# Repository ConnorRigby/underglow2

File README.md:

# Underglow 2

Automotive PMU designed for controlling external lighting.

## Specs

|high side output|low side output|12v digital input|BLE|Radio|
|-|-|-|-|-|
|2|6|4|1|1|

## Repository Structure

|folder|description|
|-|-|
|[docs](docs/README.md)|Documentation for hardware as well as 3d models and interactive bill of materials|
|[hardware](hardware/README.md)|Source material for the hardware PCB design|

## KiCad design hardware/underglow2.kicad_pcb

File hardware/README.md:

# coneRGB Underglow Controller Hardware Design

Source material for the PCB design. Designed using KiCAD intended to
be produced at PCBWay using parts from LCSC.

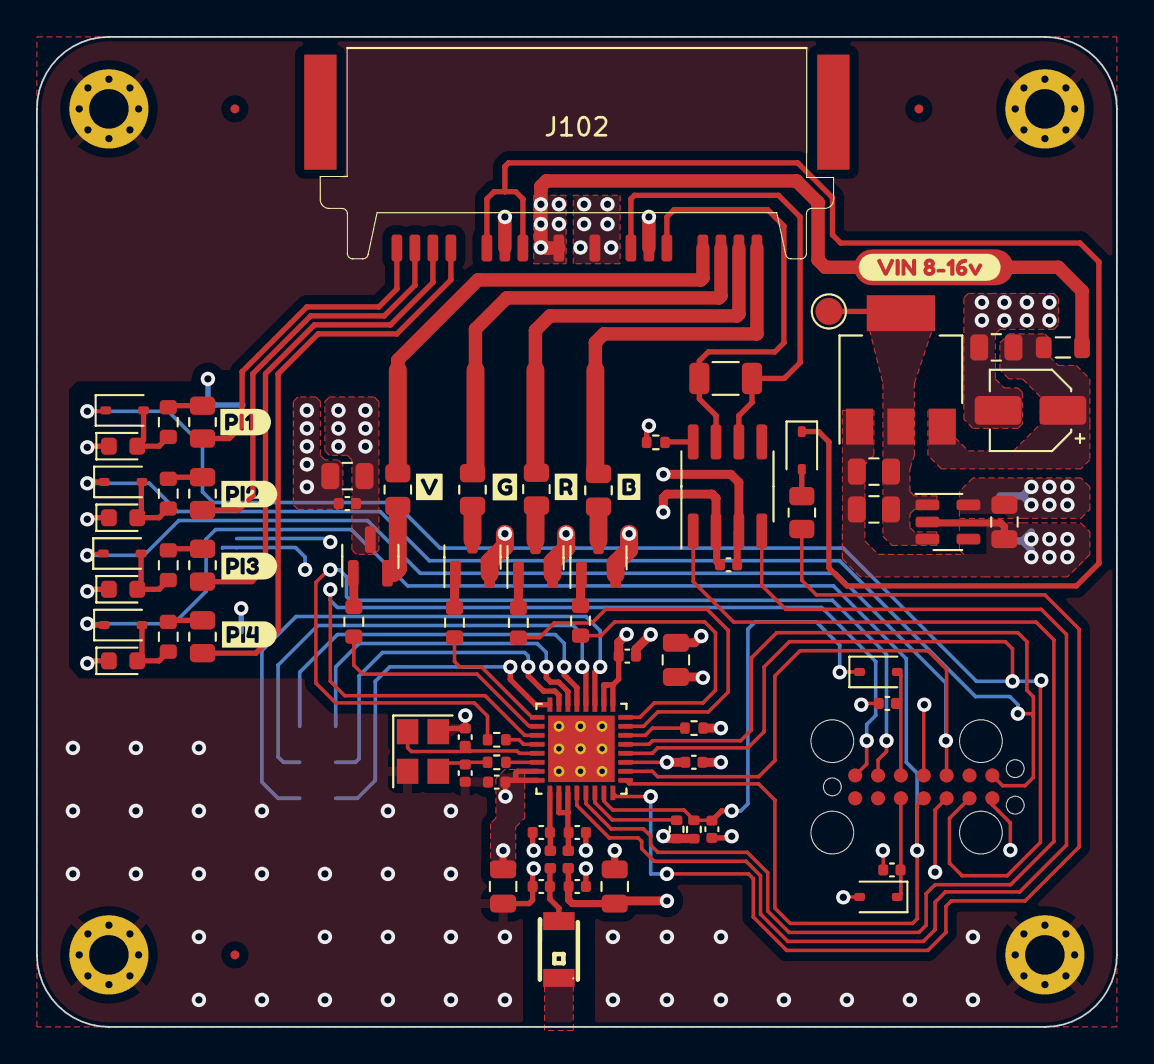
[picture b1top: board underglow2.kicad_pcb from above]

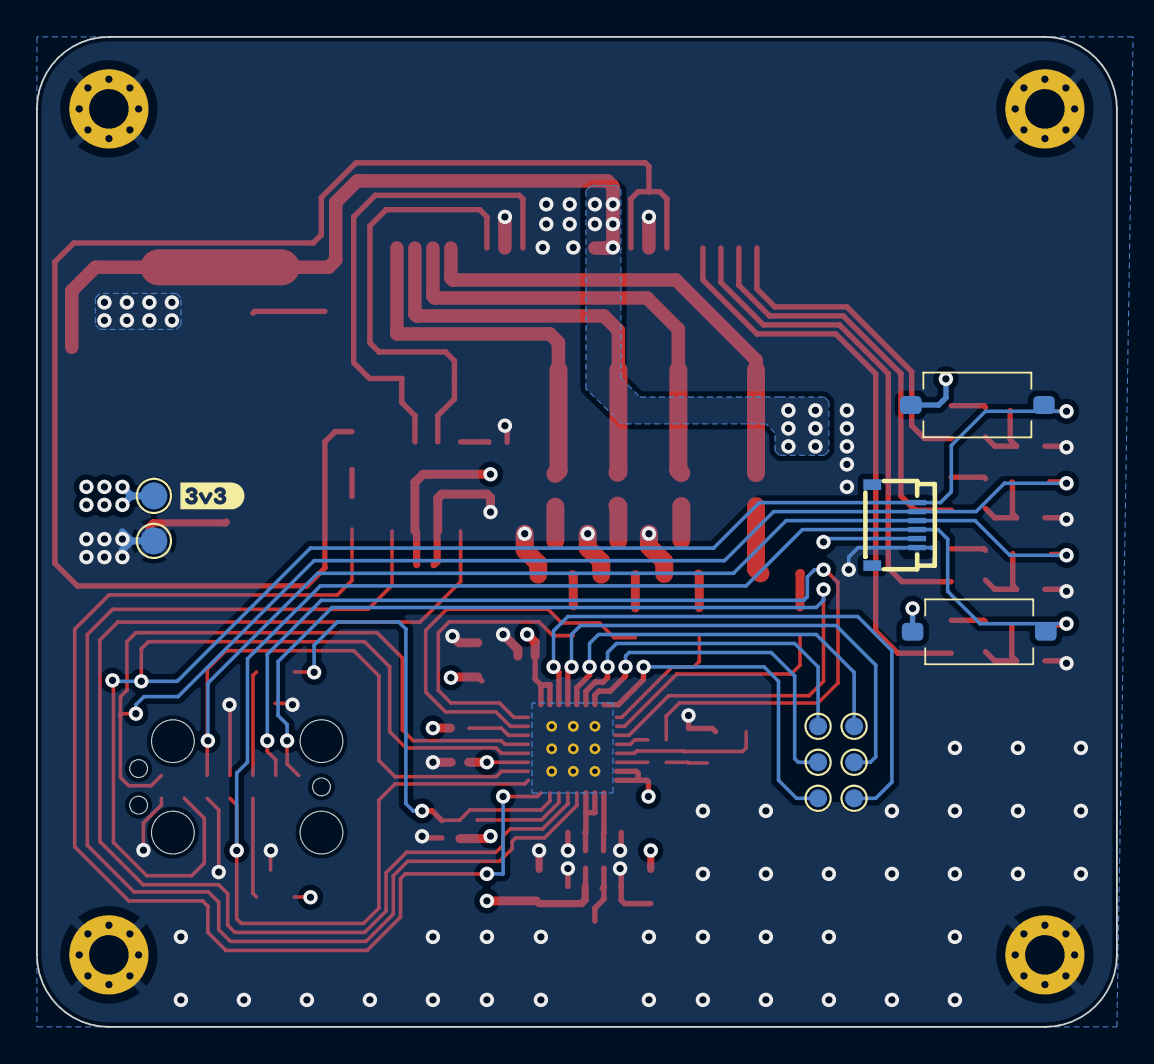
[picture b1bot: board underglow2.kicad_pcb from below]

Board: 4 copper layers, 60.0 x 55.0 mm, 99 parts (12 on the bottom side), 65 nets.

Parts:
AE101: Antenna_Chip; ANT-SMD_L3.2-W1.6
C1: 22uF; CP_Elec_4x5.4
C2, C108, C117: C_0805_10u_X5R; C_0805_2012Metric
C3, C116: 4.7uF; C_0805_2012Metric
C101, C106, C113: C_0805_1u_X7R; C_0805_2012Metric
C102, C103, C109, C110, C114, C115, C118, C119, C120: C_0402_100nf_X7R; C_0402_1005Metric
C104, C105: C_0402_18p_NP0; C_0402_1005Metric
C107: C_0402_10n_C0G; C_0402_1005Metric
C111, C112: C_0402_3p3_C0G; C_0402_1005Metric
D101, D104, D105, D106: LED_0603_RED; LED_0603_1608Metric
D102, D107, D108, D109, D110, D111, D112: 1N5819WS; D_SOD-323
FB101: 300mΩ ±25% 600Ω@100MHz; L_0805_2012Metric
H101, H102, H103, H104: MountingHole; MountingHole_2.2mm_M2_Pad_Via
J101: Conn_ST_STDC14; TC2070-IDC-FP
J102: ZE05H-16DP-2H
J104: FH34SRJ-6S-0.5SH(50); FFC-SMD_6P-P0.50_FH34SRJ-6S-0.5SH
L101: 2nH; L_0402_1005Metric
L102: 2.2nH; L_0402_1005Metric
Q101: AO3401A; SOT-23
Q102, Q103, Q104: AO3400A; SOT-23
R101, R108, R109, R110: R_0805_100; R_0805_2012Metric
R102, R113, R115, R116: R_0805_10k; R_0805_2012Metric
R103, R114, R117, R118: R_0603_1k; R_0603_1608Metric
R104, R105, R106, R107: R_0603_100; R_0603_1608Metric
R111: R_0603_220; R_0805_2012Metric
R119, R123, R124, R125: R_0402_1k; R_0402_1005Metric
R120: R_1206_DNP; R_1206_3216Metric
R121: R_0402_0; R_0402_1005Metric
R122: R_0402_499; R_0402_1005Metric
SW101, SW104: TS-1101-C-W; TS1101CW
TP1, TP2, TP3: TestPoint; TestPoint_Pad_D1.5mm
TP4, TP5, TP6, TP7, TP8, TP9: TestPoint; TestPoint_Pad_D1.0mm
U1: SPX3819M5-L-3-3/TR; SOT-23-5
U101: ESP32-C3FH4; QFN50P500X500X90-33N
U102: SN65HVD230; SOIC-8_3.9x4.9mm_P1.27mm
U103: SPX1117M3-L-5-0/TR; SOT-223-3_TabPin2
Y101: 40_Mhz; Crystal_SMD_3225-4Pin_3.2x2.5mm
kibuzzard-648F92C0: G***; kibuzzard-648F92C0
kibuzzard-648F92CD: G***; kibuzzard-648F92CD
kibuzzard-648F92E2: G***; kibuzzard-648F92E2
kibuzzard-648F92EC: G***; kibuzzard-648F92EC
kibuzzard-648F93A2: G***; kibuzzard-648F93A2
kibuzzard-648F93D4: G***; kibuzzard-648F93D4
kibuzzard-648F933E: G***; kibuzzard-648F933E
kibuzzard-648F9315: G***; kibuzzard-648F9315
kibuzzard-648F9323: G***; kibuzzard-648F9323
kibuzzard-648F9331: G***; kibuzzard-648F9331

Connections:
+5V: C2.1, C116.1, TP1.1, U1.1 (IN), U1.3 (EN), U103.2 (VO)
/B_GATE: R107.1, U101.16 (GPIO10)
/B_OUT: J102.6, R110.2
/CAN_H: J102.14, R120.1, U102.7 (CANH)
/CAN_L: J102.13, R120.2, U102.6 (CANL)
/CAN_RXD: U101.4 (XTAL_32K_P), U102.4 (R)
/CAN_TXD: U101.5 (XTAL_32K_N), U102.1 (D)
/EN: C120.1, D107.1 (K), R123.2, U101.7 (CHIP_EN)
/G_GATE: R106.1, U101.25 (GPIO18)
/G_OUT: J102.5, R109.2
/JTRST: C119.1, D107.2 (A), J101.12 (~RST)
/LNA_IN: C111.1, L102.1, U101.1 (LNA_IN)
/MTCK: D111.1 (K), J101.6 (JCLK/SWCLK), J104.6, SW104.1, U101.12 (MTCK)
/MTDI: D110.1 (K), J101.10 (JTDI/NC), J104.4, U101.10 (MTDI)
/MTDO: D112.1 (K), J101.8 (JTDO/SWO), J104.5, U101.13 (MTDO)
/MTMS: D108.1 (K), J101.4 (JTMS/SWDIO), J104.3, SW101.1, U101.9 (MTMS)
/NRZ1: R111.1, U101.8 (GPIO3)
/NZR1_OUT: D102.1 (K), J102.9, J102.10
/PI1: J102.8, R102.1
/PI1_DIV: D101.2 (A), D108.2 (A), R103.2
/PI2: J102.2, R113.1
/PI2_DIV: D104.2 (A), D110.2 (A), R114.2
/PI3: J102.7, R115.1
/PI3_DIV: D105.2 (A), D112.2 (A), R117.2
/PI4: J102.1, R116.1
/PI4_DIV: D106.2 (A), D111.2 (A), R118.2
/RF_ANT: AE101.2 (PCB_Trace), C112.1, L102.2
/R_GATE: R105.1, U101.15 (GPIO9)
/R_OUT: J102.16, R108.2
/SPICLK: TP7.1, U101.22 (SPICLK)
/SPICS0: TP6.1, U101.21 (SPICS0)
/SPID: TP8.1, U101.23 (SPID)
/SPIHD: TP4.1, U101.19 (SPIHD)
/SPIQ: TP9.1, U101.24 (SPIQ)
/SPIWP: TP5.1, U101.20 (SPIWP)
/VCP_RX: J101.14 (VCP_TX), U101.27 (U0RXD)
/VCP_TX: J101.13 (VCP_RX), R122.2
/V_GATE: R104.1, U101.26 (GPIO19)
/V_OUT: J102.15, R101.2
/XTAL_N: C105.1, U101.29 (XTAL_N), Y101.1
/XTAL_P: R121.2, U101.30 (XTAL_P)
/_VCP_TX: R122.1, U101.28 (U0TXD)
/_XTAL_P: C104.1, R121.1, Y101.3
GND: C1.2, C2.2, C3.2, C101.2, C102.2, C103.2, C104.2, C105.2, C106.2, C107.2, C108.2, C109.2, C110.2, C111.2, C112.2, C113.2, C114.2, C115.2, C116.2, C117.2, C118.2, C119.2, C120.2, D101.1 (K), D104.1 (K), D105.1 (K), D106.1 (K), H101.1, H102.1, H103.1, H104.1, J101.5 (GND), J101.7 (GND), J101.11 (GNDDetect), J102.3, J102.4, J102.12, J104.1, Q102.2 (S), Q103.2 (S), Q104.2 (S), R119.2, TP3.1, U1.2 (GND), U101.33 (GND), U102.2 (GND), U103.1 (GND), Y101.2, Y101.4
unnamed: C110.1, L101.1, U101.2 (VDD3P3), U101.3 (VDD3P3)
unnamed: D102.2 (A), R111.2
unnamed: C118.1, D109.1 (K), J101.3 (VCC)
unnamed: Q101.1 (G), R104.2
unnamed: Q101.2 (S), R101.1
unnamed: Q102.3 (D), R108.1
unnamed: Q102.1 (G), R105.2
unnamed: Q103.3 (D), R109.1
unnamed: Q103.1 (G), R106.2
unnamed: Q104.3 (D), R110.1
unnamed: Q104.1 (G), R107.2
unnamed: R102.2, R103.1
unnamed: R113.2, R114.1
unnamed: R115.2, R117.1
unnamed: R116.2, R118.1
unnamed: R124.2, U101.6 (GPIO2)
unnamed: R125.2, U101.14 (GPIO8)
unnamed: R119.1, U102.8 (Rs)
unnamed: C1.1, C3.1, FB101.2, U103.3 (VI)
VDD: C103.1, C106.1, C107.1, C108.1, C109.1, C113.1, C114.1, C115.1, C117.1, D109.2 (A), J104.2, L101.2, R123.1, R124.1, R125.1, SW101.2, SW104.2, TP2.1, U1.5 (OUT), U101.11 (VDD3P3_RTC), U101.17 (VDD3P3_CPU), U101.18 (VDD_SPI), U101.31 (VDDA), U101.32 (VDDA), U102.3 (VCC)
VS: C101.1, C102.1, FB101.1, J102.11, Q101.3 (D)

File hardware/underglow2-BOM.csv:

Item,Qty,Reference(s),Value,LibPart,Footprint,Datasheet,DNP,Capacitance,Color,Frequency,LCSC,MOSFET_TYPE,MPN,Resistance,Temperature,Tolerance,Voltage
1,1,AE101,Antenna_Chip,Device:Antenna_Chip,LCSC_Antenna:ANT-SMD_L3.2-W1.6,https://datasheet.lcsc.com/lcsc/1810241140_YAGEO-ANT3216LL00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,,,,,C293767,,C293767,,,,
2,1,C1,22uF,Device:C_Polarized_Small,Capacitor_SMD:CP_Elec_4x5.4,https://datasheet.lcsc.com/lcsc/2304140030_ROQANG-RVT1C220M0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,,,,,C72502,,RVT1C220M0405,,,,
3,3,"C2, C108, C117",C_0805_10u_X5R,LCSC_Capacitor:C_0805_10u_X5R,Capacitor_SMD:C_0805_2012Metric,https://datasheet.lcsc.com/lcsc/2304140030_Samsung-Electro-M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,,10uF,,,C15850,,CL21A106KAYNNNE,,X5R,10%,35V
4,2,"C3, C116",4.7uF,Device:C_Small,Capacitor_SMD:C_0805_2012Metric,https://datasheet.lcsc.com/lcsc/2304140030_Samsung-Electro-M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,,,,,C1779,,CL21A475KAQNNNE,,,,
5,8,"C103, C109, C110, C114, C115, C118, C119, C120",C_0402_100nf_X7R,LCSC_Capacitor:C_0402_100nf_X7R,Capacitor_SMD:C_0402_1005Metric,https://datasheet.lcsc.com/lcsc/2304140030_Samsung-Electro-M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,,100nf,,,C1525,,CL05B104KO5NNNC,,X7R,,50V
6,2,"C104, C105",C_0402_18p_NP0,LCSC_Capacitor:C_0402_DNP,Capacitor_SMD:C_0402_1005Metric,https://datasheet.lcsc.com/lcsc/2304140030_FH--Guangdong-Fen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,,18pF,,,C1549,,0402CG180J500NT,,,,
7,2,"C106, C113",C_0805_1u_X7R,LCSC_Capacitor:C_0805_1u_X7R,Capacitor_SMD:C_0805_2012Metric,https://datasheet.lcsc.com/lcsc/2304140030_Samsung-Electro-M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,,1uF,,,C28323,,CL21B105KBFNNNE,,X7R,10%,16V
8,1,C107,C_0402_10n_C0G,LCSC_Capacitor:C_0402_10n_C0G,Capacitor_SMD:C_0402_1005Metric,https://datasheet.lcsc.com/lcsc/2304140030_Samsung-Electro-M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,,10nf,,,C15195,,CL05B103KB5NNNC,,C0G,±5%,35V
9,2,"C111, C112",C_0402_3p3_C0G,LCSC_Capacitor:C_0402_DNP,Capacitor_SMD:C_0402_1005Metric,https://datasheet.lcsc.com/lcsc/2304140030_FH--Guangdong-Fen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,,3.3pF,,,C1565,,0402CG3R3C500NT,,,,
10,4,"D101, D104, D105, D106",LED_0603_RED,LCSC_LED:LED_0603_RED,LED_SMD:LED_0603_1608Metric,https://datasheet.lcsc.com/lcsc/1912111437_MEIHUA-MHT192CRCT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,,,Red,,C389517,,MHT192CRCT,,,,
11,7,"D102, D107, D108, D109, D110, D111, D112",1N5819WS,Diode:1N5819WS,Diode_SMD:D_SOD-323,https://datasheet.lcsc.com/lcsc/2204281430_Guangdong-Hottech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,,,,,C191023,,1N5819WS,,,,
12,1,FB101,300mΩ ±25% 600Ω@100MHz,Device:FerriteBead_Small,Inductor_SMD:L_0805_2012Metric,https://datasheet.lcsc.com/lcsc/2109181830_Sunlord-GZ2012D60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,,,,,C1017,,GZ2012D601TF,,,,
13,1,J102,ZE05H-16DP-2H,Connector_Generic_MountingPin:Conn_01x16_MountingPin,Harness:ZE05-16DS-HU,https://datasheet.lcsc.com/lcsc/2211031030_HRS-Hirose-ZE05H-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,,,,,C5242960,,ZE05H-16DP-2H,,,,
14,1,J103,ZE05-16DS-HU/R,Connector_Generic_MountingPin:Conn_01x16_MountingPin,Harness:ZE05-16DS-HU,~,,,,,C3267442,,ZE05-16DS-HU/R,,,,
15,1,L101,2nH,Device:L_Small,Inductor_SMD:L_0402_1005Metric,https://datasheet.lcsc.com/lcsc/2304140030_Chilisin-Elec-CLH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,,,,,C142239,,CLH1005T-2N0S-S-NP,,,,
16,1,L102,2.2nH,Device:L_Small,Inductor_SMD:L_0402_1005Metric,https://datasheet.lcsc.com/lcsc/2304140030_Chilisin-Elec-CLH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,,,,,C142238,,CLH1005T-2N2S-S-NP,,,,
17,1,Q101,AO3401A,Transistor_FET:AO3401A,Package_TO_SOT_SMD:SOT-23,http://www.aosmd.com/pdfs/datasheet/AO3401A.pdf,,,,,C15127,P-Channel,AO3401A,,,,
18,3,"Q102, Q103, Q104",AO3400A,Transistor_FET:AO3400A,Package_TO_SOT_SMD:SOT-23,http://www.aosmd.com/pdfs/datasheet/AO3400A.pdf,,,,,C20917,N-Channel,AO3400A,,,,
19,4,"R101, R108, R109, R110",R_0805_100,LCSC_Resistor:R_0805_DNP,Resistor_SMD:R_0805_2012Metric,https://datasheet.lcsc.com/lcsc/2206010216_UNI-ROYAL-Uniroya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,,,,,C17408,,0805W8F1000T5E,100Ω,,,
20,4,"R102, R113, R115, R116",R_0805_10k,LCSC_Resistor:R_0805_10k,Resistor_SMD:R_0805_2012Metric,https://datasheet.lcsc.com/lcsc/2206010216_UNI-ROYAL-Uniroya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,,,,,C17414,,0805W8F1002T5E,10kΩ,,,
21,4,"R103, R114, R117, R118",R_0603_1k,LCSC_Resistor:R_0603_DNP,Resistor_SMD:R_0603_1608Metric,https://datasheet.lcsc.com/lcsc/2206010130_UNI-ROYAL-Uniroya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,,,,,C21190,,0603WAF1001T5E,1kΩ,,,
22,4,"R104, R105, R106, R107",R_0603_100,LCSC_Resistor:R_0603_DNP,Resistor_SMD:R_0603_1608Metric,https://datasheet.lcsc.com/lcsc/2206010130_UNI-ROYAL-Uniroya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,,,,,C22775,,0603WAF1000T5E,100Ω,,,
23,1,R111,R_0603_220,LCSC_Resistor:R_0805_DNP,Resistor_SMD:R_0805_2012Metric,https://datasheet.lcsc.com/lcsc/2304140030_YAGEO-RC0603FR-07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,,,,,C17557,,0805W8F2200T5E,220Ω,,,
24,4,"R119, R123, R124, R125",R_0402_1k,LCSC_Resistor:R_0402_1k,Resistor_SMD:R_0402_1005Metric,https://datasheet.lcsc.com/lcsc/2206010216_UNI-ROYAL-Uniroya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,,,,,C11702,,0402WGF1001TCE,1kΩ,,,
25,1,R121,R_0402_0,LCSC_Resistor:R_0402_DNP,Resistor_SMD:R_0402_1005Metric,https://datasheet.lcsc.com/lcsc/2206010216_UNI-ROYAL-Uniroya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,,,,,C17168,,0402WGF0000TCE,0Ω,,,
26,1,R122,R_0402_499,LCSC_Resistor:R_0402_499,Resistor_SMD:R_0402_1005Metric,https://datasheet.lcsc.com/lcsc/2202281730_YAGEO-RT0402BRD07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,,,,,C852807,,RT0402BRD07499RL,499Ω,,,
27,16,"T101, T102, T103, T104, T105, T106, T107, T108, T109, T110, T111, T112, T113, T114, T115, T116",ZE05-2022SCF,Connector:Conn_01x01_Pin,Harness:ZE05-2022SCF,~,,,,,C570453,,ZE05-2022SCF,,,,
28,1,U1,SPX3819M5-L-3-3/TR,Regulator_Linear:SPX3819M5-L-3-3,Package_TO_SOT_SMD:SOT-23-5,https://datasheet.lcsc.com/lcsc/2304140030_MaxLinear-SPX3819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,,,,,C9055,,SPX3819M5-L-3-3/TR,,,,
29,1,U101,ESP32-C3FH4,LCSC_Microcontroller:ESP32-C3FH4,LCSC_Microcontroller:QFN50P500X500X90-33N,https://www.mouser.com/datasheet/2/891/esp32_c3_datasheet_en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,,,,,C2858491,,ESP32-C3FH4,,,,
30,1,U102,SN65HVD230,Interface_CAN_LIN:SN65HVD230,Package_SO:SOIC-8_3.9x4.9mm_P1.27mm,http://www.ti.com/lit/ds/symlink/sn65hvd230.pdf,,,,,C12084,,SN65HVD230DR,,,,
31,1,U103,SPX1117M3-L-5-0/TR ,Regulator_Linear:AP1117-50,Package_TO_SOT_SMD:SOT-223-3_TabPin2,https://datasheet.lcsc.com/lcsc/2304140030_MaxLinear-SPX1117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,,,,,C6187,,SPX1117M3-L-5-0/TR,,,,
32,1,Y101,40_Mhz,LCSC_Crystal:40_Mhz,Crystal:Crystal_SMD_3225-4Pin_3.2x2.5mm,https://datasheet.lcsc.com/lcsc/2110101030_Shenzhen-SCTF-Ele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,,,,40Mhz,C2901712,,SX3B40.000F1210F30,,,,

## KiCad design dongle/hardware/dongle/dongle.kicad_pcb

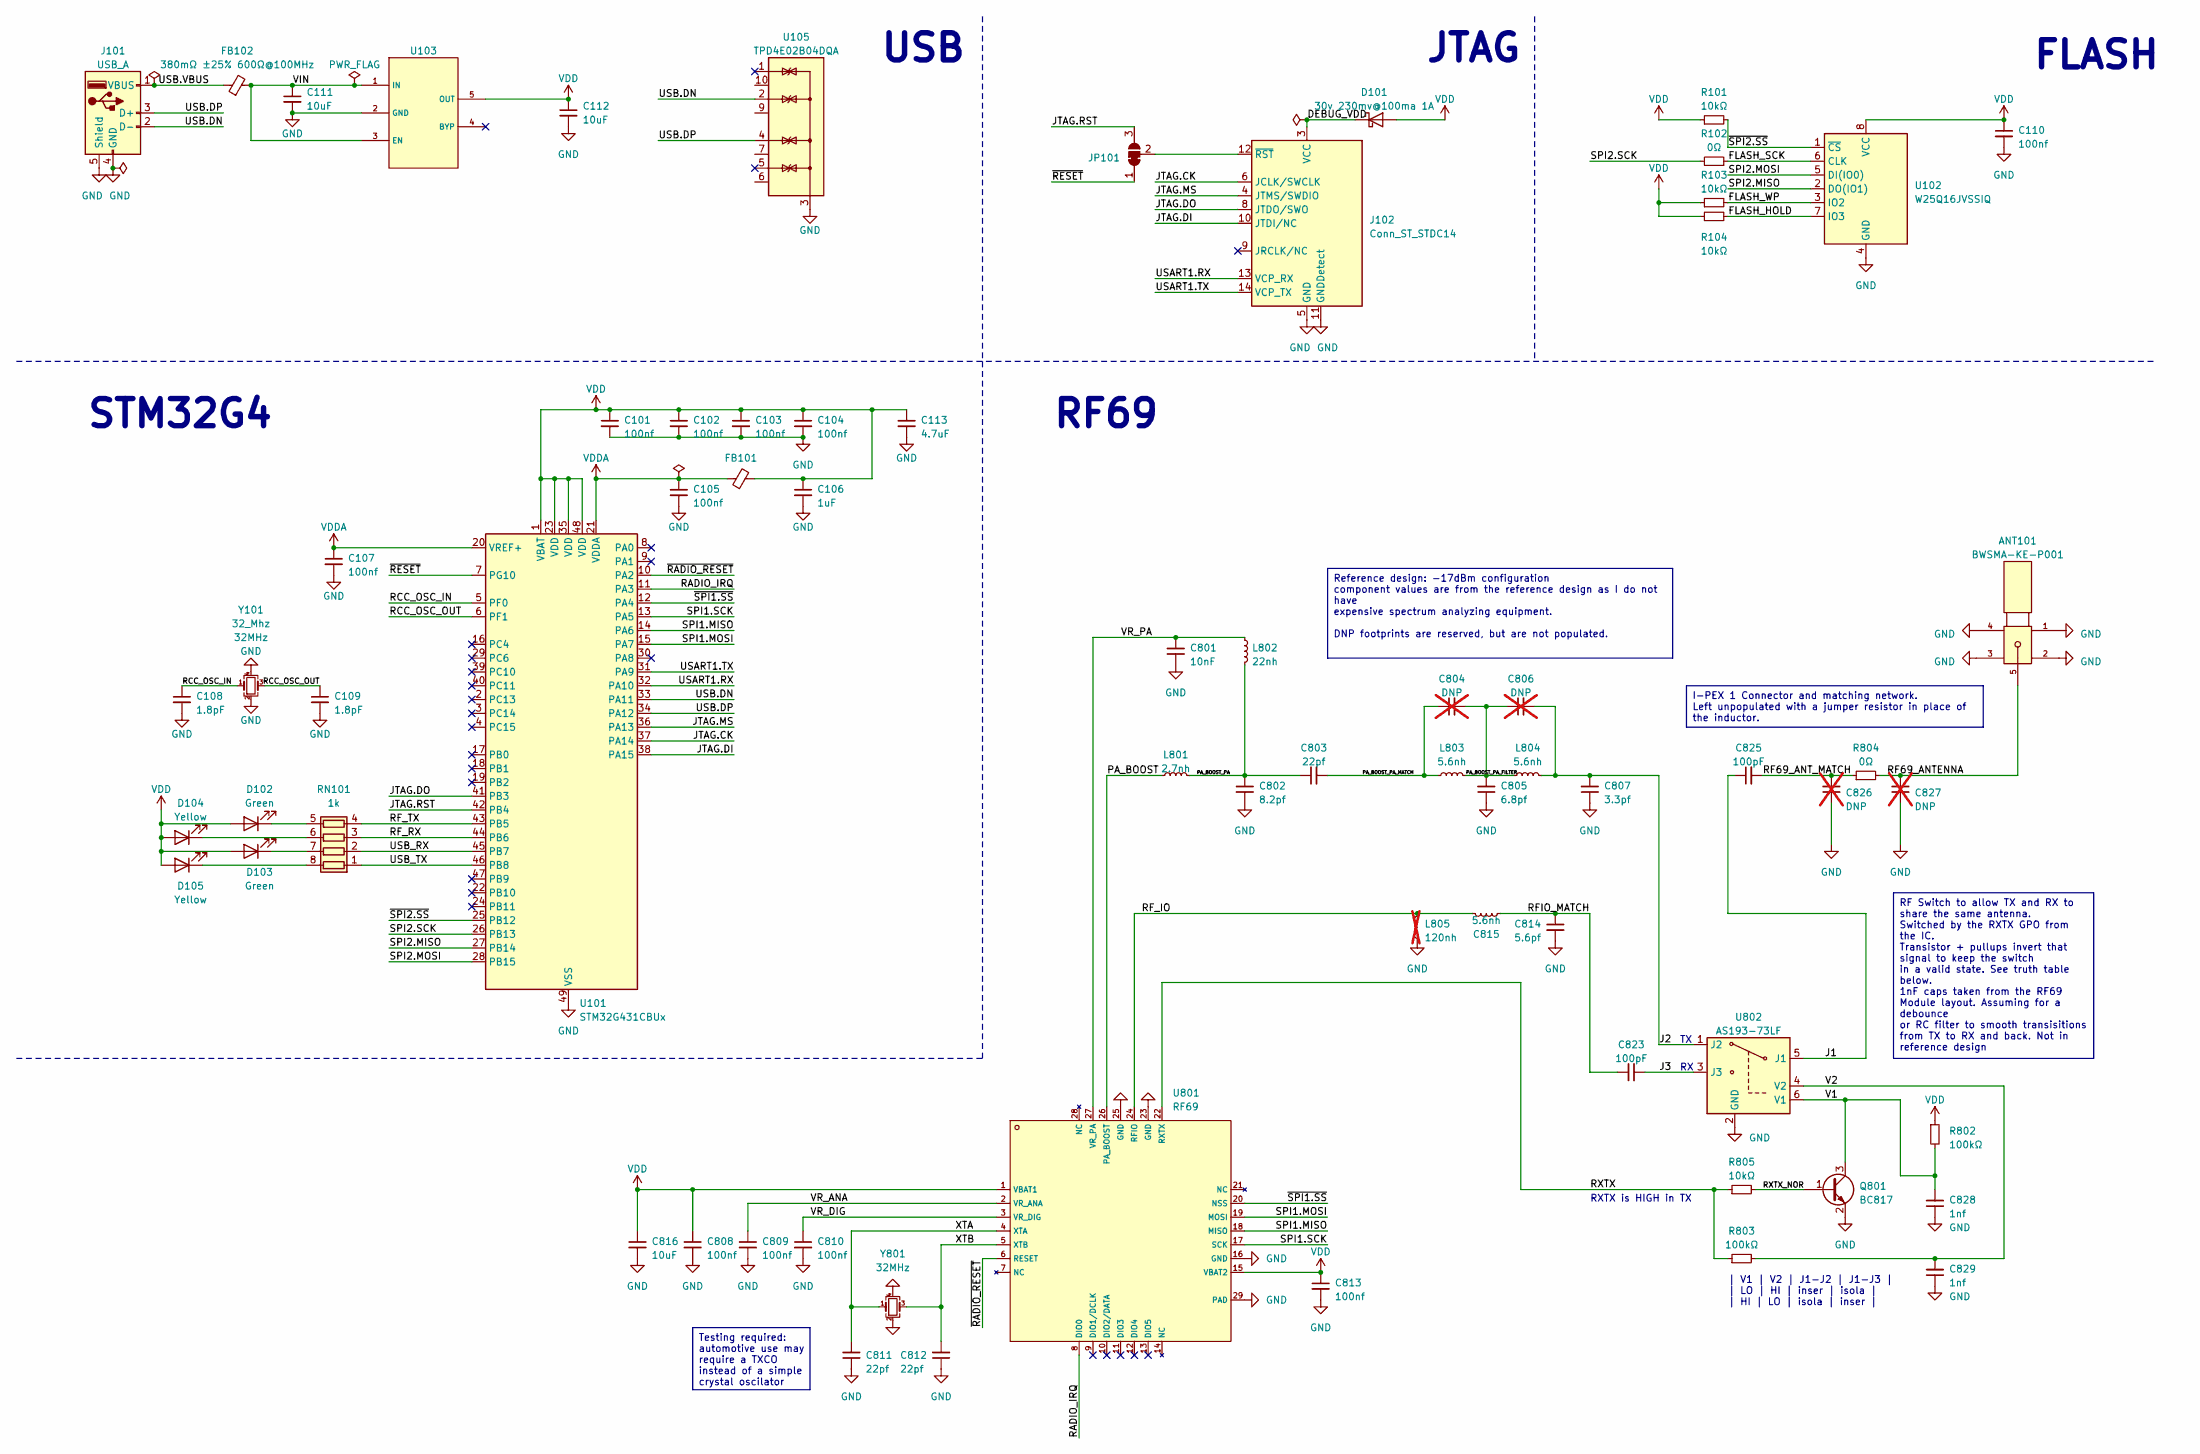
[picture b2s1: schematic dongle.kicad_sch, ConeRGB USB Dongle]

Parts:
ANT101: BWSMA-KE-P001; SMA-SMD_BWSMA-KE-P001; LCSC C496550
C101, C102, C103, C104, C105, C107, C110, C808, C809, C810, C813: C_0402_100nf_X7R; C_0402_1005Metric; Voltage 50V; MPN 0402B104K500NT; LCSC C110251
C106: C_0402_1u_X5R; C_0402_1005Metric; Voltage 35V; MPN CL05A105KL5NRNC; LCSC C307413
C108, C109: C_0402_1p8_C0G; C_0402_1005Metric; Voltage 50V; Tolerance 1%; MPN GJM1555C1H1R8WB01D; LCSC C76903
C111, C112, C816: C_0805_10u_X5R; C_0805_2012Metric; Voltage 35V; Tolerance 10%; MPN GRM21BR6YA106KE43L; LCSC C162422
C113: C_0805_4u7_X5R; C_0805_2012Metric; Voltage 6.3; Tolerance 20%; MPN CC0805MKX5R5BB475; LCSC C577033
C801: C_0402_10n_C0G; C_0402_1005Metric; Voltage 50V; Tolerance ±10%; MPN CC0402KRX7R9BB103; LCSC C60133
C802: C_0402_8p2_C0G; C_0402_1005Metric; Voltage 50V; Tolerance 2%; MPN GJM1555C1H8R2CB01D; LCSC C88898
C803, C811, C812: C_0402_22p_C0G; C_0402_1005Metric; Voltage 50V; Tolerance 2%; MPN GJM1555C1H220GB01D; LCSC C161315
C804, C806, C826, C827: C_0402_DNP; C_0402_1005Metric; not fitted
C805: C_0402_6p8_C0G; C_0402_1005Metric; Voltage 50V; Tolerance 2%; MPN GCM1555C1H6R8BA16D; LCSC C354360
C807: C_0402_3p3_C0G; C_0402_1005Metric; Voltage 50V; Tolerance 2%; MPN GRM1555C1H3R3CA01D; LCSC C76968
C814: C_0402_5p6_C0G; C_0402_1005Metric; Voltage 50V; Tolerance 2%; MPN GJM1555C1H5R6CB01D; LCSC C88895
C815: L_0402_5n6; L_0402_1005Metric; MPN LQW15AN5N6C10D; LCSC C91626
C823, C825: C_0402_100p_C0G; C_0402_1005Metric; Voltage 50V; Tolerance 5%; MPN GRT1555C1H101JA02D; LCSC C711072
C828, C829: C_0402_1nf_X7R; C_0402_1005Metric; Voltage 100V; MPN GCM155R72A102KA37D; LCSC C126538
D101: 30v 230mv@100ma 1A; D_SOD-323F; MPN CUS10S30,H3F; LCSC C146335
D102, D103: LED_0603_GREEN; LED_0603_1608Metric; MPN MHT192UGCT; LCSC C389519
D104, D105: LED_0603_YELLOW; LED_0603_1608Metric; MPN 19-213/Y2C-CQ2R2L/3T(CY); LCSC C72038
FB101: L_0402_1005Metric; LCSC C102745
FB102: 380mΩ ±25% 600Ω@100MHz; L_0603_1608Metric; LCSC C19330
J101: USB_A; USB-A-TH_48037-0001; LCSC C136455
J102: Conn_ST_STDC14; TC2070-IDC-FP
JP101: SolderJumper_3_Bridged12; SolderJumper-3_P1.3mm_Bridged12_RoundedPad1.0x1.5mm_NumberL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
L801: L_0402_2n7; L_0402_1005Metric; MPN LQW15AN2N7C00D; LCSC C98058
L802: L_0402_22n; L_0402_1005Metric; MPN LQW15AN22NG00D; LCSC C86129
L803, L804: L_0402_5n6; L_0402_1005Metric; MPN LQW15AN5N6C10D; LCSC C91626
L805: L_0402_120n; L_0402_1005Metric; MPN LQW15ANR12J00D; LCSC C113123; not fitted
Q801: BC817; SOT-23; LCSC C39828
R101, R103, R104, R805: R_0402_10k; R_0402_1005Metric; MPN ARG02BTC1002; LCSC C2902636
R102, R804: R_0402_0; R_0402_1005Metric; MPN RTT020000FTH; LCSC C102745
R802, R803: R_0402_100k; R_0402_1005Metric; MPN ARG02BTC1003; LCSC C2984406
RN101: 1k; R_Array_Concave_4x0603; LCSC C20197
U101: STM32G431CBUx; QFN-48-1EP_7x7mm_P0.5mm_EP5.6x5.6mm; LCSC C529356
U102: W25Q16JVSSIQ; SOIC-8_5.23x5.23mm_P1.27mm; MPN W25Q16JVSSIQ; LCSC C82317
U103: SPX3819M5-L-3-3_TR; SOT-23-5; LCSC C9055
U105: TPD4E02B04DQA; USON-10_2.5x1.0mm_P0.5mm; MPN TPD4E02B04DQA; LCSC C106794
U801: RF69; QFN-28-1EP_5x5mm_P0.5mm_EP3.75x3.75mm_ThermalVias; MPN RF69; LCSC C77220
U802: AS193-73LF; SOT-23-6; MPN AS193-73LF; LCSC C6199
Y101: 32_Mhz; Crystal_SMD_3225-4Pin_3.2x2.5mm; MPN TAXM32M4RLBCDT2T; LCSC C5143379
Y801: 32_Mhz; Crystal_SMD_3225-4Pin_3.2x2.5mm; MPN X322532MOB4SI; LCSC C9009

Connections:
/DEBUG_VDD: D101.1 (K), J102.3 (VCC)
/FLASH_HOLD: R104.2, U102.7 (IO3)
/FLASH_SCK: R102.1, U102.6 (CLK)
/FLASH_WP: R103.2, U102.3 (IO2)
/J1: C825.1, U802.5 (J1)
/J2: C806.2, C807.2, L804.2, U802.1 (J2)
/J3: C823.2, U802.3 (J3)
/JTAG.CK: J102.6 (JCLK/SWCLK), U101.37 (PA14)
/JTAG.DI: J102.10 (JTDI/NC), U101.38 (PA15)
/JTAG.DO: J102.8 (JTDO/SWO), U101.41 (PB3)
/JTAG.MS: J102.4 (JTMS/SWDIO), U101.36 (PA13)
/JTAG.RST: JP101.3 (B), U101.42 (PB4)
/PA_BOOST: L801.1, U801.26 (PA_BOOST)
/PA_BOOST_PA: C802.1, C803.1, L801.2, L802.2
/PA_BOOST_PA_FILTER: C804.2, C805.2, C806.1, L803.2, L804.1
/PA_BOOST_PA_MATCH: C803.2, C804.1, L803.1
/RADIO_IRQ: U101.11 (PA3), U801.8 (DIO0)
/RCC_OSC_IN: C108.1, U101.5 (PF0), Y101.1
/RCC_OSC_OUT: C109.1, U101.6 (PF1), Y101.3
/RF69_ANTENNA: ANT101.5, C827.2, R804.2
/RF69_ANT_MATCH: C825.2, C826.2, R804.1
/RFIO_MATCH: C814.1, C815.1, C823.1
/RF_IO: C815.2, L805.2, U801.24 (RFIO)
/RF_RX: RN101.3 (R3.1), U101.44 (PB6)
/RF_TX: RN101.4 (R4.1), U101.43 (PB5)
/RXTX: R803.1, R805.1, U801.22 (RXTX)
/RXTX_NOR: Q801.1 (B), R805.2
/SPI1.MISO: U101.14 (PA6), U801.18 (MISO)
/SPI1.MOSI: U101.15 (PA7), U801.19 (MOSI)
/SPI1.SCK: U101.13 (PA5), U801.17 (SCK)
/SPI2.MISO: U101.27 (PB14), U102.2 (DO(IO1))
/SPI2.MOSI: U101.28 (PB15), U102.5 (DI(IO0))
/SPI2.SCK: R102.2, U101.26 (PB13)
/USART1.RX: J102.13 (VCP_RX), U101.32 (PA10)
/USART1.TX: J102.14 (VCP_TX), U101.31 (PA9)
/USB.DN: J101.2 (D-), U101.33 (PA11); also elsewhere on the board
/USB.DP: J101.3 (D+), U101.34 (PA12); also elsewhere on the board
/USB.VBUS: FB102.1, J101.1 (VBUS)
/USB_RX: RN101.2 (R2.1), U101.45 (PB7)
/USB_TX: RN101.1 (R1.1), U101.46 (PB8)
/V1: C828.2, Q801.3 (C), R802.2, U802.6 (V1)
/V2: C829.2, R803.2, U802.4 (V2)
/VIN: C111.1, FB102.2, U103.1 (IN), U103.3 (EN)
/VR_ANA: C809.1, U801.2 (VR_ANA)
/VR_DIG: C810.1, U801.3 (VR_DIG)
/VR_PA: C801.1, L802.1, U801.27 (VR_PA)
/XTA: C811.2, U801.4 (XTA), Y801.1
/XTB: C812.2, U801.5 (XTB), Y801.3
/~RADIO_RESET: U101.10 (PA2), U801.6 (RESET)
/~RESET: JP101.1 (A), U101.7 (PG10)
/~SPI1.SS: U101.12 (PA4), U801.20 (NSS)
/~SPI2.SS: R101.2, U101.25 (PB12), U102.1 (~CS)
GND: ANT101.1, ANT101.2, ANT101.3, ANT101.4, C101.2, C102.2, C103.2, C104.2, C105.2, C106.2, C107.2, C108.2, C109.2, C110.2, C111.2, C112.2, C113.2, C801.2, C802.2, C805.1, C807.1, C808.2, C809.2, C810.2, C811.1, C812.1, C813.2, C814.2, C816.2, C826.1, C827.1, C828.1, C829.1, J101.4 (GND), J101.5 (Shield), J102.5 (GND), J102.7 (GND), J102.11 (GNDDetect), L805.1, Q801.2 (E), U101.49 (VSS), U102.4 (GND), U103.2 (GND), U801.16 (GND), U801.23 (GND), U801.25 (GND), U801.29 (PAD), U802.2 (GND), Y101.2, Y101.4, Y801.2, Y801.4; also elsewhere on the board
unnamed: D102.1 (K), RN101.5 (R4.2)
unnamed: D103.1 (K), RN101.7 (R2.2)
unnamed: D104.1 (K), RN101.6 (R3.2)
unnamed: D105.1 (K), RN101.8 (R1.2)
unnamed: J102.12 (~RST), JP101.2 (C)
VDD: C101.1, C102.1, C103.1, C104.1, C106.1, C110.1, C112.1, C113.1, C808.1, C813.1, C816.1, D101.2 (A), D102.2 (A), D103.2 (A), D104.2 (A), D105.2 (A), FB101.2, R101.1, R103.1, R104.1, R802.1, U101.1 (VBAT), U101.23 (VDD), U101.35 (VDD), U101.48 (VDD), U102.8 (VCC), U103.5 (OUT), U801.1 (VBAT1), U801.15 (VBAT2)
VDDA: C105.1, C107.1, FB101.1, U101.20 (VREF+), U101.21 (VDDA)

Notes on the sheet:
I-PEX 1 Connector and matching network. Left unpopulated with a jumper resistor in place of the inductor.
Testing required: automotive use may require a TXCO instead of a simple crystal oscilator
RF Switch to allow TX and RX to share the same antenna. Switched by the RXTX GPO from the IC. Transistor + pullups invert that signal to keep the switch in a valid state. See truth table below. 1nF caps taken from the RF69 Module layout. Assuming for a debounce or RC filter to smooth transisitions 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
Reference design: -17dBm configuration component values are from the reference design as I do not have expensive spectrum analyzing equipment. DNP footprints are reserved, but are not populated.
RF69
FLASH
STM32G4
JTAG
USB
RXTX is HIGH in TX
| V1 | V2 | J1-J2 | J1-J3 | | LO | HI | inser | isola | | HI | LO | isola | inser |

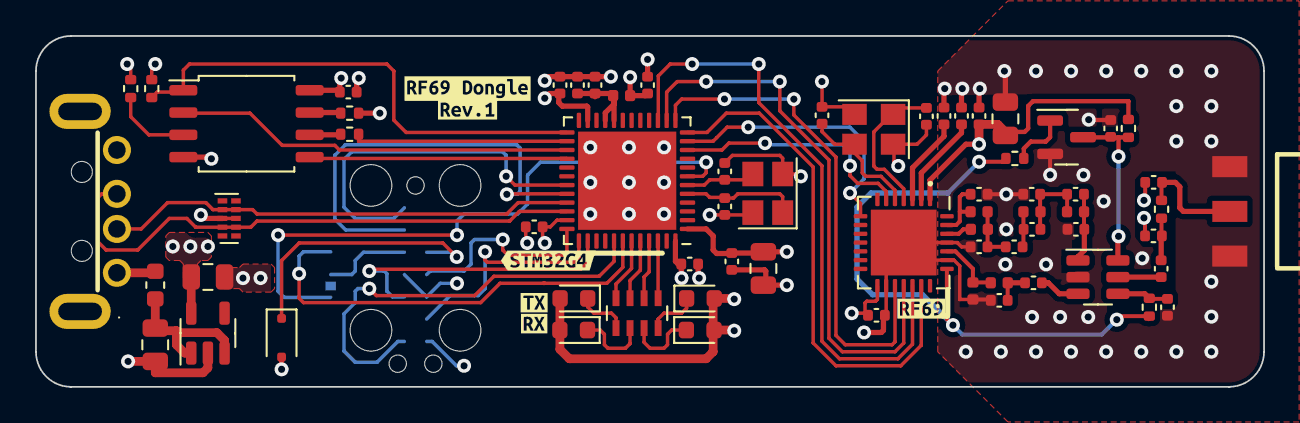
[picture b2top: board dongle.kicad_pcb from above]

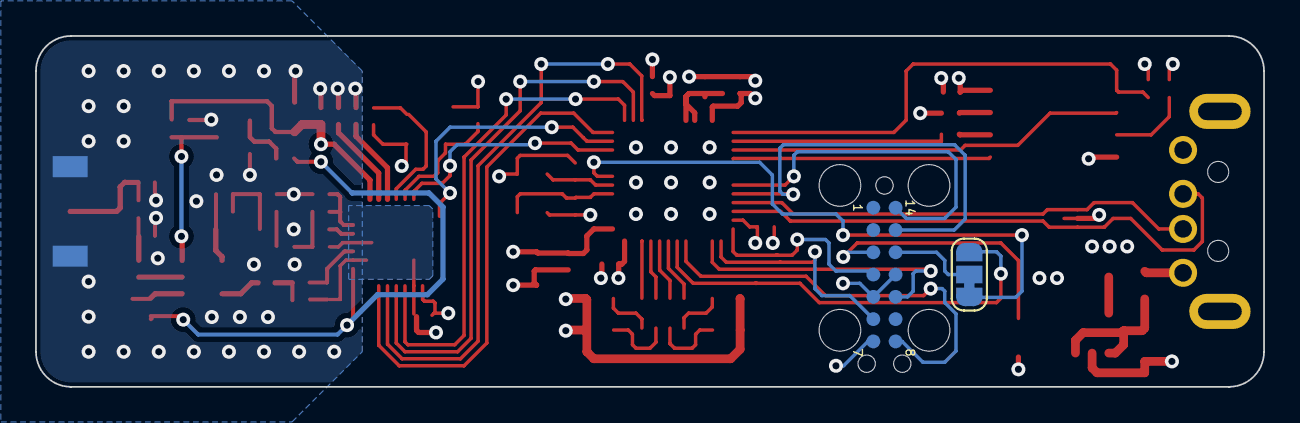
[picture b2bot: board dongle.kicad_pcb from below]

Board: 4 copper layers, 70.0 x 20.0 mm, 75 parts (2 on the bottom side), 60 nets.

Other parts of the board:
U104: TPD4E02B04DQA; USON-10_2.5x1.0mm_P0.5mm
kibuzzard-645835C4: G***; kibuzzard-645835C4
kibuzzard-645835D2: G***; kibuzzard-645835D2
kibuzzard-64583550: G***; kibuzzard-64583550
kibuzzard-64583571: G***; kibuzzard-64583571
kibuzzard-64583646: G***; kibuzzard-64583646
kibuzzard-64583712: G***; kibuzzard-64583712

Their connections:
/USB.DN: U104.2 (IO2); also elsewhere on the board
/USB.DP: U104.4 (IO3); also elsewhere on the board
GND: U104.3 (G), U104.8 (G); also elsewhere on the board

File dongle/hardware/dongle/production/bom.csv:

Designator,Footprint,Quantity,Value,LCSC Part #
ANT101,SMA-SMD_BWSMA-KE-P001,1,BWSMA-KE-P001,C496550
"C101, C102, C103, C104, C105, C107, C110, C808, C809, C810, C813",0402,11,C_0402_100nf_X7R,C110251
C106,0402,1,C_0402_1u_X5R,C307413
"C108, C109",0402,2,C_0402_1p8_C0G,C76903
"C111, C112, C816",0805,3,C_0805_10u_X5R,C162422
C113,0805,1,C_0805_4u7_X5R,C577033
C801,0402,1,C_0402_10n_C0G,C60133
C802,0402,1,C_0402_8p2_C0G,C88898
"C803, C811, C812",0402,3,C_0402_22p_C0G,C161315
C805,0402,1,C_0402_6p8_C0G,C354360
C807,0402,1,C_0402_3p3_C0G,C76968
C814,0402,1,C_0402_5p6_C0G,C88895
"C815, L803, L804",0402,3,L_0402_5n6,C91626
"C823, C825",0402,2,C_0402_100p_C0G,C711072
"C828, C829",0402,2,C_0402_1nf_X7R,C126538
D101,D_SOD-323F,1,30v 230mv@100ma 1A,C146335
"D102, D103",0603,2,LED_0603_GREEN,C389519
"D104, D105",0603,2,LED_0603_YELLOW,C72038
FB101,0402,1,~,C102745
FB102,0603,1,380mΩ ±25% 600Ω@100MHz,C19330
J101,USB-A-TH_48037-0001,1,USB_A,C136455
JP101,SolderJumper-3_P1.3mm_Bridged12_RoundedPad1.0x1.5mm_NumberLabels,1,SolderJumper_3_Bridged12,
L801,0402,1,L_0402_2n7,C98058
L802,0402,1,L_0402_22n,C86129
Q801,SOT-23,1,BC817,C39828
"R101, R103, R104, R805",0402,4,R_0402_10k,C2902636
"R102, R804",0402,2,R_0402_0,C102745
"R802, R803",0402,2,R_0402_100k,C2984406
U101,QFN-48-1EP_7x7mm_P0.5mm_EP5.6x5.6mm,1,STM32G431CBUx,C529356
U102,SOIC-8_5.23x5.23mm_P1.27mm,1,W25Q16JVSSIQ,C82317
U103,SOT-23-5,1,SPX3819M5-L-3-3_TR,C9055
U104,USON-10_2.5x1.0mm_P0.5mm,1,TPD4E02B04DQA,C106794
U801,QFN-28-1EP_5x5mm_P0.5mm_EP3.75x3.75mm_ThermalVias,1,RF69,C77220
U802,SOT-23-6,1,AS193-73LF,C6199
"Y101, Y801",Crystal_SMD_3225-4Pin_3.2x2.5mm,2,32_Mhz,C5143379
